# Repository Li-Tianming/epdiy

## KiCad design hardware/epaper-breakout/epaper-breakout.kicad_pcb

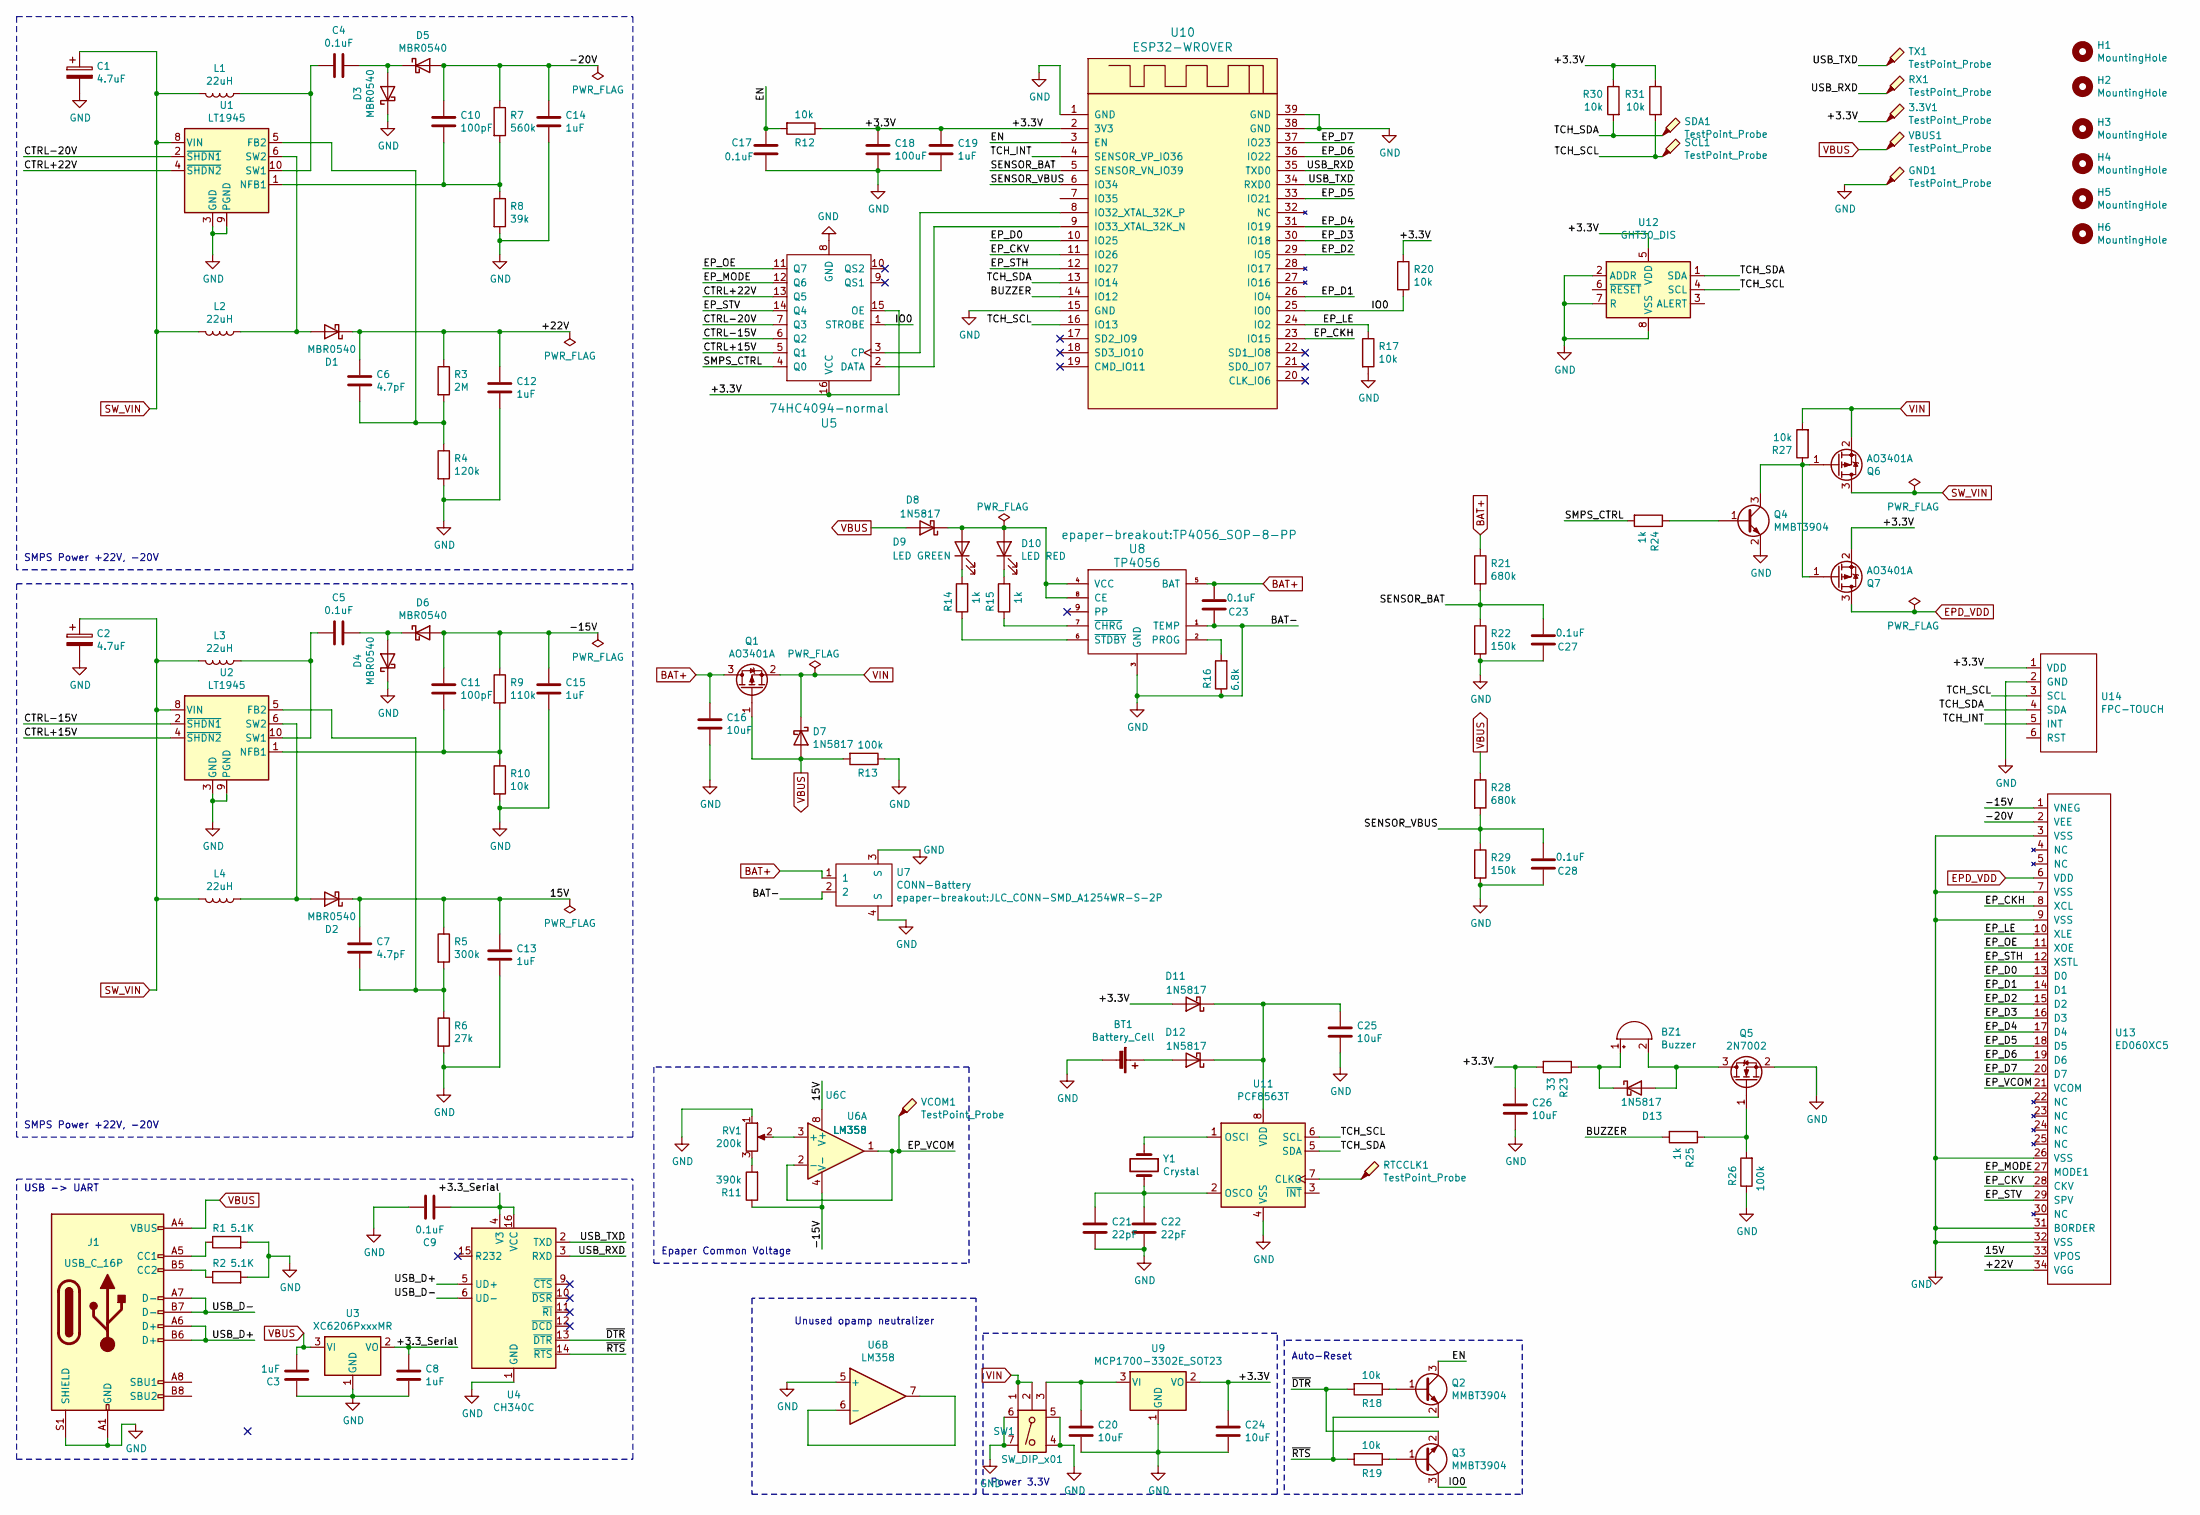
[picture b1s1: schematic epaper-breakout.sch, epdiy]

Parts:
3.3V1: TestPoint_Probe; TestPoint_Pad_D1.0mm
BT1: Battery_Cell; JLC_BAT-SMD_MY-1220-03; LCSC C964818
BZ1: Buzzer; JLC_BUZ-SMD_4P-L8.5-W8.5_FUET-8530-05; LCSC C417429
C1, C2: 4.7uF; C_0603_1608Metric; LCSC C19666
C3, C8, C12, C13, C14, C15, C19: 1uF; C_0603_1608Metric; LCSC C15849
C4, C5, C9, C23, C27, C28: 0.1uF; C_0603_1608Metric; LCSC C14663
C6, C7: 4.7pF; C_0603_1608Metric; LCSC C1669
C10, C11: 100pF; C_0603_1608Metric; LCSC C14858
C16, C20, C24, C25, C26: 10uF; C_0603_1608Metric; LCSC C19702
C17: 0.1uF; C_0603_1608Metric; LCSC C1588
C18: 100uF; CP_EIA-3528-15_AVX-H; LCSC C16133
C21, C22: 22pF; C_0603_1608Metric; LCSC C105620
D1, D2, D3, D4, D5, D6: MBR0540; D_SOD-123; LCSC C21353
D7, D8, D11, D12, D13: 1N5817; D_SOD-123; LCSC C8598
D9: LED GREEN; LED_0805_2012Metric; LCSC C2297
D10: LED RED; LED_0805_2012Metric; LCSC C84256
GND1: TestPoint_Probe; TestPoint_Pad_D1.0mm
H1, H2, H3, H4, H5, H6: MountingHole; MountingHole_2.2mm_M2
J1: USB_C_16P; JLC_USB-C-SMD_TYPE-C-31-M-13C; LCSC C2835312
L1, L2, L3, L4: 22uH; JLC_IND-SMD_L4.0-W4.0_SMNR4020; LCSC C135264
Q1, Q6, Q7: AO3401A; SOT-23; LCSC C15127
Q2, Q3, Q4: MMBT3904; SOT-23; LCSC C20526
Q5: 2N7002; SOT-23; LCSC C916396
R1, R2: 5.1K; R_0805_2012Metric; LCSC C17656
R3: 2M; R_0805_2012Metric; LCSC C26112
R4: 120k; R_0805_2012Metric; LCSC C17436
R5: 300k; R_0805_2012Metric; LCSC C17616
R6: 27k; R_0805_2012Metric; LCSC C17593
R7: 560k; R_0805_2012Metric; LCSC C15785
R8: 39k; R_0805_2012Metric; LCSC C25826
R9: 110k; R_0805_2012Metric; LCSC C17422
R10, R12, R17, R18, R19, R20, R27, R30, R31: 10k; R_0805_2012Metric; LCSC C17414
R11: 390k; R_0805_2012Metric; LCSC C17656
R13: 100k; R_0805_2012Metric; LCSC C149504
R14, R15, R24, R25: 1k; R_0805_2012Metric; LCSC C17513
R16: 6.8k; R_0805_2012Metric; LCSC C17772
R21, R28: 680k; R_0805_2012Metric; LCSC C17797
R22, R29: 150k; R_0805_2012Metric; LCSC C17470
R23: 33; R_0603_1608Metric; LCSC C72812
R26: 100k; R_0805_2012Metric; LCSC C17407
RTCCLK1: TestPoint_Probe; TestPoint_Pad_D1.0mm
RV1: 200k; JLC_RES-ADJ-SMD_VG039NCH; LCSC C128551
RX1: TestPoint_Probe; TestPoint_Pad_D1.0mm
SCL1: TestPoint_Probe; TestPoint_Pad_D1.0mm
SDA1: TestPoint_Probe; TestPoint_Pad_D1.0mm
SW1: SW_DIP_x01; JLC_SW-SMD_MK-12C02-G025; LCSC C778186
TX1: TestPoint_Probe; TestPoint_Pad_D1.0mm
U1, U2: LT1945; MSOP-10_3x3mm_P0.5mm; LCSC C665600
U3: XC6206PxxxMR; SOT-23; LCSC C5446
U4: CH340C; SOIC-16_3.9x9.9mm_P1.27mm; LCSC C84681
U5: 74HC4094-normal; SOIC-16_3.9x9.9mm_P1.27mm; LCSC C5651
U6: LM358; SOP-8_3.76x4.96mm_P1.27mm
U7: CONN-Battery; JLC_CONN-SMD_A1254WR-S-2P; LCSC C272975
U8: TP4056; TP4056_SOP-8-PP; LCSC C16581
U9: MCP1700-3302E_SOT23; SOT-23; LCSC C39051
U10: ESP32-WROVER; LCSC C503591
U11: PCF8563T; SOIC-8_3.9x4.9mm_P1.27mm; LCSC C7440
U12: GHT30_DIS; Sensirion_DFN-8-1EP_2.5x2.5mm_P0.5mm_EP1.1x1.7mm; LCSC C2758005
U13: ED060XC5; JLC_FFC-SMD_34P-P0.50_FH34SRJ-34S-0.5SH; LCSC C528053
U14: FPC-TOUCH; JLC_FFC-SMD_6P-P0.50_FH34SRJ-6S-0.5SH; LCSC C224194
VBUS1: TestPoint_Probe; TestPoint_Pad_D1.0mm
VCOM1: TestPoint_Probe; TestPoint_Pad_D1.0mm
Y1: Crystal; JLC_CRYSTAL-SMD_L7.0-W3.2-LS7.5; LCSC C1122370

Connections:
/15V: C7.2, C13.2, D2.1 (K), R5.1, U6.8 (V+), U13.33 (VPOS)
/+3.3V: 3.3V1.1, C18.1, C19.2, C24.2, C26.2, D11.2 (A), Q7.2 (S), R12.1, R20.1, R23.2, R30.1, R31.1, U5.15 (OE), U5.16 (VCC), U9.2 (VO), U10.2 (3V3), U12.5 (VDD), U14.1 (VDD)
/+3.3_Serial: C8.2, C9.1, U3.2 (VO), U4.4 (V3), U4.16 (VCC)
/+22V: C6.2, C12.2, D1.1 (K), R3.1, U13.34 (VGG)
/-15V: C11.2, C15.2, D6.2 (A), R9.1, R11.1, U6.4 (V-), U13.1 (VNEG)
/-20V: C10.2, C14.2, D5.2 (A), R7.1, U13.2 (VEE)
/BUZZER: R25.2, U10.14 (IO12)
/CTRL+15V: U2.4 (~SHDN2), U5.5 (Q1)
/CTRL+22V: U1.4 (~SHDN2), U5.13 (Q5)
/CTRL-15V: U2.2 (~SHDN1), U5.6 (Q2)
/CTRL-20V: U1.2 (~SHDN1), U5.7 (Q3)
/EN: C17.1, Q2.3 (C), R12.2, U10.3 (EN)
/EP_CKH: U10.23 (IO15), U13.8 (XCL)
/EP_CKV: U10.11 (IO26), U13.28 (CKV)
/EP_D0: U10.10 (IO25), U13.13 (D0)
/EP_D1: U10.26 (IO4), U13.14 (D1)
/EP_D2: U10.29 (IO5), U13.15 (D2)
/EP_D3: U10.30 (IO18), U13.16 (D3)
/EP_D4: U10.31 (IO19), U13.17 (D4)
/EP_D5: U10.33 (IO21), U13.18 (D5)
/EP_D6: U10.36 (IO22), U13.19 (D6)
/EP_D7: U10.37 (IO23), U13.20 (D7)
/EP_LE: R17.1, U10.24 (IO2), U13.10 (XLE)
/EP_MODE: U5.12 (Q6), U13.27 (MODE1)
/EP_OE: U5.11 (Q7), U13.11 (XOE)
/EP_STH: U10.12 (IO27), U13.12 (XSTL)
/EP_STV: U5.14 (Q4), U13.29 (SPV)
/EP_VCOM: U6.1, U6.2 (-), U13.21 (VCOM), VCOM1.1
/IO0: Q3.3 (C), R20.2, U5.1 (STROBE), U10.25 (IO0)
/SENSOR_BAT: C27.2, R21.2, R22.1, U10.5 (SENSOR_VN_IO39)
/SENSOR_VBUS: C28.2, R28.2, R29.1, U10.6 (IO34)
/SMPS_CTRL: R24.2, U5.4 (Q0)
/TCH_INT: U10.4 (SENSOR_VP_IO36), U14.5 (INT)
/TCH_SCL: R31.2, SCL1.1, U10.16 (IO13), U11.6 (SCL), U12.4 (SCL), U14.3 (SCL)
/TCH_SDA: R30.2, SDA1.1, U10.13 (IO14), U11.5 (SDA), U12.1 (SDA), U14.4 (SDA)
/USB_D+: J1.A6 (D+), J1.B6 (D+), U4.5 (UD+)
/USB_D-: J1.A7 (D-), J1.B7 (D-), U4.6 (UD-)
/USB_RXD: RX1.1, U4.3 (RXD), U10.35 (TXD0)
/USB_TXD: TX1.1, U4.2 (TXD), U10.34 (RXD0)
/~DTR: Q3.2 (E), R18.2, U4.13 (~DTR)
/~RTS: Q2.2 (E), R19.2, U4.14 (~RTS)
BAT+: C16.1, C23.2, Q1.3 (D), R21.1, U7.1, U8.5 (BAT)
EPD_VDD: Q7.3 (D), U13.6 (VDD)
GND: BT1.2 (-), C1.2, C2.2, C3.2, C8.1, C9.2, C12.1, C13.1, C14.1, C15.1, C16.2, C17.2, C18.2, C19.1, C20.1, C21.2, C22.2, C23.1, C24.1, C25.1, C26.1, C27.1, C28.1, D3.1 (K), D4.1 (K), GND1.1, J1.A1 (GND), J1.A12 (GND), J1.B1 (GND), J1.B12 (GND), J1.S1 (SHIELD), Q4.2 (E), Q5.2 (S), R1.2, R2.2, R4.2, R6.2, R8.2, R10.2, R13.1, R16.1, R17.2, R22.2, R26.1, R29.2, RV1.1, SW1.4 (Shield), SW1.5 (Shield), SW1.6 (Shield), SW1.7 (Shield), U1.3 (GND), U1.7 (PGND), U1.9 (PGND), U2.3 (GND), U2.7 (PGND), U2.9 (PGND), U3.1 (GND), U4.1 (GND), U5.8 (GND), U6.5 (+), U7.2, U7.3 (S), U7.4 (S), U8.1 (TEMP), U8.3 (GND), U9.1 (GND), U10.1 (GND), U10.15 (GND), U10.38 (GND), U10.39 (GND), U11.4 (VSS), U12.2 (ADDR), U12.7 (R), U12.8 (VSS), U12.9 (VSS), U13.3 (VSS), U13.7 (VSS), U13.9 (VSS), U13.26 (VSS), U13.31 (BORDER), U13.32 (VSS), U14.2 (GND)
unnamed: BT1.1 (+), D12.2 (A)
unnamed: BZ1.1 (-), D13.1 (K), R23.1
unnamed: BZ1.2 (+), D13.2 (A), Q5.3 (D)
unnamed: C4.1, D3.2 (A), D5.1 (K)
unnamed: C4.2, L1.1, U1.10 (SW1)
unnamed: C5.1, D4.2 (A), D6.1 (K)
unnamed: C5.2, L3.1, U2.10 (SW1)
unnamed: C6.1, R3.2, R4.1, U1.5 (FB2)
unnamed: C7.1, R5.2, R6.1, U2.5 (FB2)
unnamed: C10.1, R7.2, R8.1, U1.1 (NFB1)
unnamed: C11.1, R9.2, R10.1, U2.1 (NFB1)
unnamed: C20.2, SW1.3, U9.3 (VI)
unnamed: C21.1, C22.1, U11.2 (OSCO), Y1.2
unnamed: C25.2, D11.1 (K), D12.1 (K), U11.8 (VDD)
unnamed: D1.2 (A), L2.1, U1.6 (SW2)
unnamed: D2.2 (A), L4.1, U2.6 (SW2)
unnamed: D9.1 (K), R14.2
unnamed: D10.1 (K), R15.2
unnamed: D8.1 (K), D9.2 (A), D10.2 (A), U8.4 (VCC), U8.8 (CE)
unnamed: J1.A5 (CC1), R1.1
unnamed: J1.B5 (CC2), R2.1
unnamed: Q2.1 (B), R18.1
unnamed: Q3.1 (B), R19.1
unnamed: Q4.1 (B), R24.1
unnamed: Q4.3 (C), Q6.1 (G), Q7.1 (G), R27.1
unnamed: Q5.1 (G), R25.1, R26.2
unnamed: R11.2, RV1.3
unnamed: R14.1, U8.6 (~STDBY)
unnamed: R15.1, U8.7 (~CHRG)
unnamed: R16.2, U8.2 (PROG)
unnamed: RTCCLK1.1, U11.7 (CLKO)
unnamed: RV1.2, U6.3 (+)
unnamed: U6.6 (-), U6.7
unnamed: U5.3 (CP), U10.8 (IO32_XTAL_32K_P)
unnamed: U5.2 (DATA), U10.9 (IO33_XTAL_32K_N)
unnamed: U11.1 (OSCI), Y1.1
SW_VIN: C1.1, C2.1, L1.2, L2.2, L3.2, L4.2, Q6.3 (D), U1.8 (VIN), U2.8 (VIN)
VBUS: C3.1, D7.2 (A), D8.2 (A), J1.A4 (VBUS), J1.A9 (VBUS), J1.B4 (VBUS), J1.B9 (VBUS), Q1.1 (G), R13.2, R28.1, U3.3 (VI), VBUS1.1
VIN: D7.1 (K), Q1.2 (S), Q6.2 (S), R27.2, SW1.1, SW1.2

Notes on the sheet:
SMPS Power +22V, -20V
Auto-Reset
Power 3.3V
Unused opamp neutralizer
Epaper Common Voltage
USB -> UART

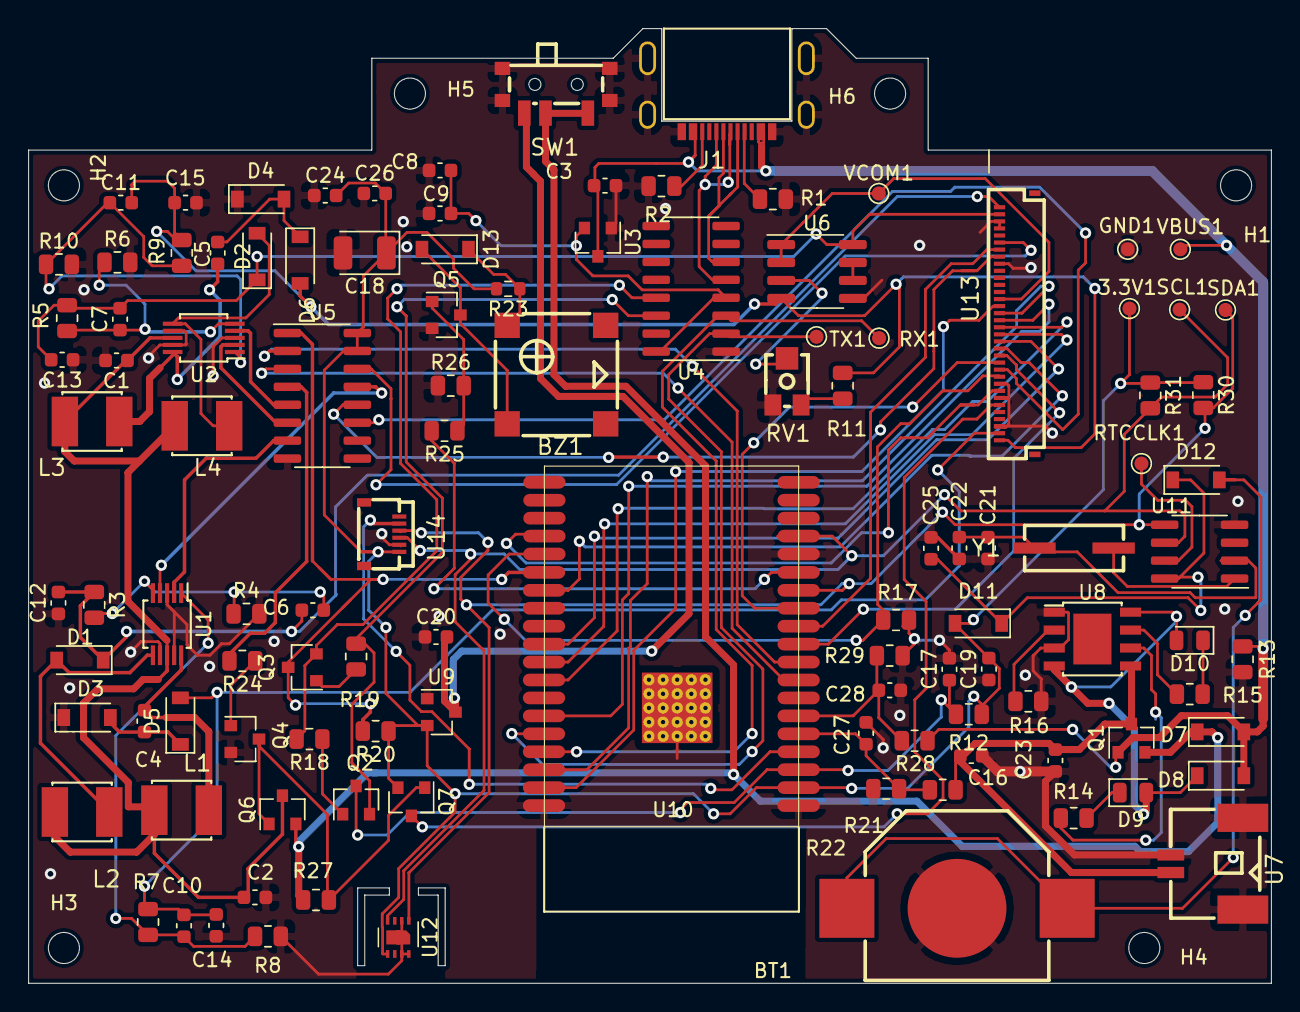
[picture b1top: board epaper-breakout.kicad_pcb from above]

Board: 2 copper layers, 88.0 x 67.6 mm, 118 parts (0 on the bottom side), 83 nets.

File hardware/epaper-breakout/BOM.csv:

Comment,Designator,Footprint,LCSC Part #
Battery_Cell Single-cell battery,BT1,JLC_BAT-SMD_MY-1220-03, C964818
"Buzzer Buzzer, polarized",BZ1,JLC_BUZ-SMD_4P-L8.5-W8.5_FUET-8530-05, C417429
4.7uF Polarized capacitor,"C1,C2",C_0603_1608Metric,C19666
1uF Unpolarized capacitor,"C3,C8,C12,C13,C14,C15,C19",C_0603_1608Metric,C15849
0.1uF Unpolarized capacitor,"C4,C5,C9,C17,C23,C27",C_0603_1608Metric,C14663
4.7pF Unpolarized capacitor,"C6,C7",C_0603_1608Metric,C1669
100pF Unpolarized capacitor,"C10,C11",C_0603_1608Metric,C14858
10uF Unpolarized capacitor,"C16,C20,C24,C25,C26",C_0603_1608Metric,C19702
100uF Unpolarized capacitor,C18,CP_EIA-3528-15_AVX-H, C16133
22pF Unpolarized capacitor,"C21,C22",C_0603_1608Metric,C105620
"MBR0540 40V 0.5A Schottky Power Rectifier Diode, SOD-123","D1,D2,D3,D4,D5,D6",D_SOD-123,C21353
"1N5817 20V 1A Schottky Barrier Rectifier Diode, DO-41","D7,D8,D11,D12,D13",D_SOD-123, C8598
LED GREEN Light emitting diode,D9,LED_0805_2012Metric,C2297
LED RED Light emitting diode,D10,LED_0805_2012Metric, C84256
USB_C_16P USB 2.0-only Type-C Receptacle connector,J1,JLC_USB-C-SMD_TYPE-C-31-M-13C,C2835312
22uH Inductor,"L1,L2,L3,L4",JLC_IND-SMD_L4.0-W4.0_SMNR4020, C135264
"AO3401A -4.0A Id, -30V Vds, P-Channel MOSFET, SOT-23","Q1,Q6,Q7",SOT-23, C15127
"MMBT3904 0.2A Ic, 40V Vce, Small Signal NPN Transistor, SOT-23","Q2,Q3,Q4",SOT-23,C20526
"2N7002 0.115A Id, 60V Vds, N-Channel MOSFET, SOT-23",Q5,SOT-23, C916396
5.1K Resistor,"R1,R2",R_0805_2012Metric,C17656
2M Resistor,R3,R_0805_2012Metric,C26112
120k Resistor,R4,R_0805_2012Metric, C17436
300k Resistor,R5,R_0805_2012Metric,  C17616
27k Resistor,R6,R_0805_2012Metric,C17593
560k Resistor,R7,R_0805_2012Metric,C15785
39k Resistor,R8,R_0805_2012Metric,C25826
110k Resistor,R9,R_0805_2012Metric,C17422
10k Resistor,"R10,R12,R17,R18,R19,R20,R27,R30,R31",R_0805_2012Metric,C17414
390k Resistor,R11,R_0805_2012Metric,C17656
100k Resistor,"R13,R26",R_0805_2012Metric,C17407
1k Resistor,"R14,R15,R24,R25",R_0805_2012Metric,C17513
6.8k Resistor,R16,R_0805_2012Metric, C17772
680k Resistor,"R21,R28",R_0805_2012Metric, C17797
150k Resistor,"R22,R29",R_0805_2012Metric, C17470
33 Resistor,R23,R_0603_1608Metric,C72812
200k Potentiometer,RV1,JLC_RES-ADJ-SMD_VG039NCH, C128551
"SW_DIP_x01 1x DIP Switch, Single Pole Single Throw (SPST) switch, small symbol",SW1,JLC_SW-SMD_MK-12C02-G025, C778186
"LT1945 Dual Micropower DC/DC Converter with Positive and Negative Outputs, MSOP-10","U1,U2",MSOP-10_3x3mm_P0.5mm,C665600
"XC6206PxxxMR Positive 60-250mA Low Dropout Regulator, Fixed Output, SOT-23",U3,SOT-23, C5446
"CH340C USB serial converter, UART, SOIC-16",U4,SOIC-16_3.9x9.9mm_P1.27mm, C84681
74HC4094-normal ,U5,SOIC-16_3.9x9.9mm_P1.27mm,C5651
"LM358 Low-Power, Dual Operational Amplifiers, DIP-8/SOIC-8/TO-99-8",U6,SOP-8_3.76x4.96mm_P1.27mm,C7950
CONN-Battery ,U7,JLC_CONN-SMD_A1254WR-S-2P,C272975
TP4056 ,U8,TP4056_SOP-8-PP, C16581
"MCP1700-3302E_SOT23 250mA Low Quiscent Current LDO, 3.3V output, SOT-23",U9,SOT-23,C39051
ESP32-WROVER ,U10,ESP32-WROVER, C503591
"PCF8563T Realtime Clock/Calendar I2C Interface, SOIC-8",U11,SOIC-8_3.9x4.9mm_P1.27mm,C7440
"GHT30_DIS I²C humidity and temperature sensor, ±2%RH, ±0.2°C, DFN-8",U12,Sensirion_DFN-8-1EP_2.5x2.5mm_P0.5mm_EP1.1x1.7mm,C2758005
ED060XC5 ED060XC5 E-Paper screen,U13,X05A20H34G,C528053
FPC-TOUCH ,U14,JLC_FFC-SMD_6P-P0.50_FH34SRJ-6S-0.5SH,C224194
Crystal Two pin crystal,Y1,JLC_CRYSTAL-SMD_L7.0-W3.2-LS7.5,C1122370

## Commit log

2021-08-25 minor change in V5
    exchange L1 <-> U2 position
    change usb connector footprint
    change U6 footprint
    chang RV1 footprint
2021-09-05 Add 3D model for connector
2022-01-26 New version board base on V5
    Add Touch screen connector
    Add RTC
    Add Buzzer
    Change USB-MicroB to USB-C
    Change Battery connector
    Change footprint
2022-01-26 Change fabrication attribute
2022-02-27 change outline
2022-03-08 Re-position connector
2022-03-08 fabrication update
2022-03-08 Add 3d models
2022-04-25 change i2c bus pin
2022-11-09 change usb-c type
    2022-08-27
2023-06-30 change FPC connector
2024-01-22 add axt334124.stp

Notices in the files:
hardware/epaper-breakout/epaper-breakout.sch:
License: CC-BY-SA-4.0
